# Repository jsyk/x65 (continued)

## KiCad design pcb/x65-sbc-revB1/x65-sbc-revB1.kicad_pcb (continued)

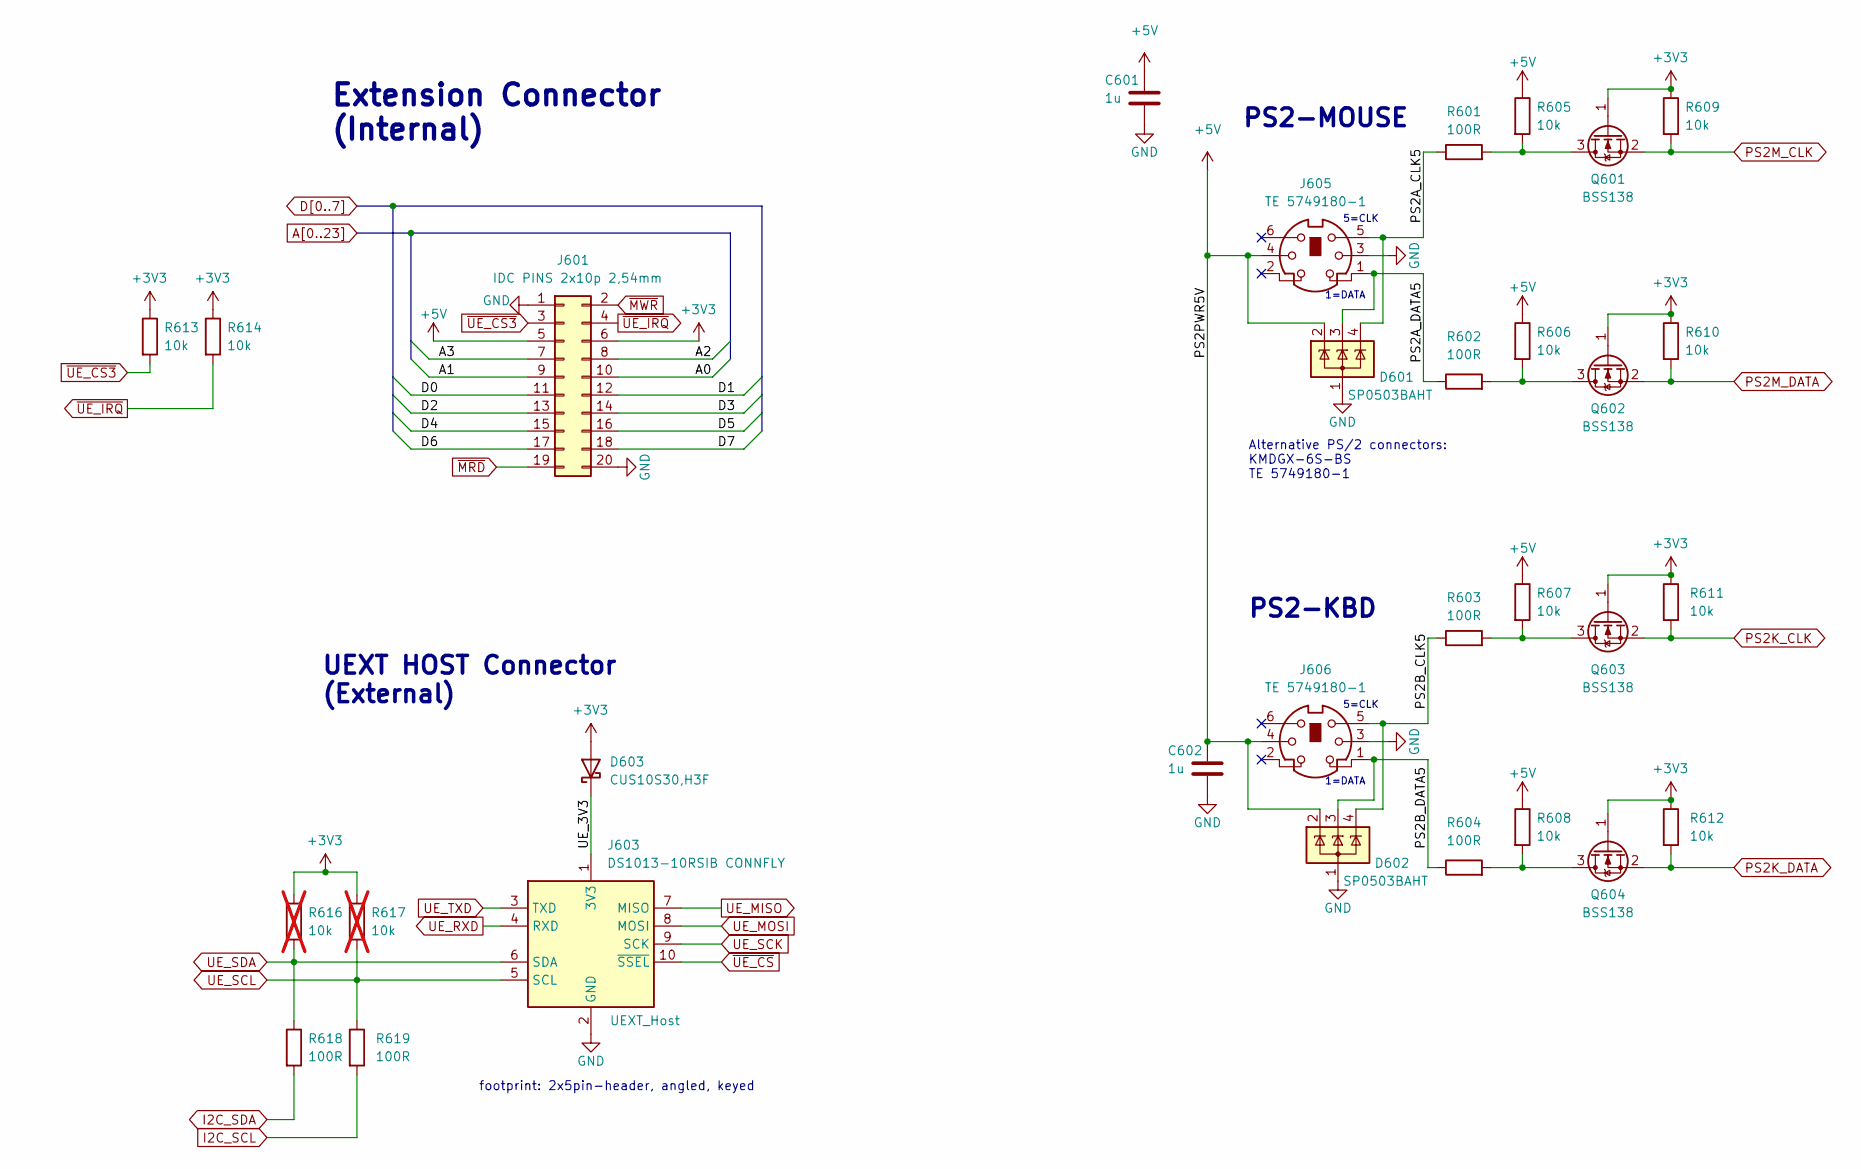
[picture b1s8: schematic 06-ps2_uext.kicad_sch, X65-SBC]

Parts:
C601, C602: 1u; C_0603_1608Metric_Pad1.08x0.95mm_HandSolder
D601, D602: SP0503BAHT; SOT-143
D603: CUS10S30,H3F; D_SOD-323_HandSoldering
J601: IDC PINS 2x10p 2,54mm; IDC-Header_2x10_P2.54mm_Vertical
J603: DS1013-10RSIB CONNFLY; IDC-Header_2x05_P2.54mm_Horizontal
J605, J606: TE 5749180-1; TE_5749180-1
Q601, Q602, Q603, Q604: BSS138; SOT-23
R601, R602, R603, R604, R618, R619: 100R; R_0603_1608Metric_Pad0.98x0.95mm_HandSolder
R605, R606, R607, R608, R609, R610, R611, R612, R613, R614: 10k; R_0603_1608Metric_Pad0.98x0.95mm_HandSolder
R616, R617: 10k; R_0603_1608Metric_Pad0.98x0.95mm_HandSolder; not fitted

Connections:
+3V3: D603.2 (A), J601.6, Q601.1 (G), Q602.1 (G), Q603.1 (G), Q604.1 (G), R609.1, R610.1, R611.1, R612.1, R613.1, R614.1, R616.1, R617.1; also elsewhere on the board
+5V: C601.1, C602.1, D601.2 (K), D602.2 (K), J601.5, J605.4, J606.4, R605.1, R606.1, R607.1, R608.1; also elsewhere on the board
/PS2 Kbd+Mouse, UEXT/PS2A_CLK5: D601.4 (K), J605.5, R601.1
/PS2 Kbd+Mouse, UEXT/PS2A_DATA5: D601.3 (K), J605.1, R602.1
/PS2 Kbd+Mouse, UEXT/PS2B_CLK5: D602.4 (K), J606.5, R603.1
/PS2 Kbd+Mouse, UEXT/PS2B_DATA5: D602.3 (K), J606.1, R604.1
/PS2 Kbd+Mouse, UEXT/UE_3V3: D603.1 (K), J603.1 (3V3)
A0: J601.10; also elsewhere on the board
A1: J601.9; also elsewhere on the board
A2: J601.8; also elsewhere on the board
A3: J601.7; also elsewhere on the board
D0: J601.11; also elsewhere on the board
D1: J601.12; also elsewhere on the board
D2: J601.13; also elsewhere on the board
D3: J601.14; also elsewhere on the board
D4: J601.15; also elsewhere on the board
D5: J601.16; also elsewhere on the board
D6: J601.17; also elsewhere on the board
D7: J601.18; also elsewhere on the board
GND: C601.2, C602.2, D601.1 (A), D602.1 (A), J601.1, J601.20, J603.2 (GND), J605.3, J606.3; also elsewhere on the board
I2C_SCL: R619.2; also elsewhere on the board
I2C_SDA: R618.2; also elsewhere on the board
unnamed: Q601.3 (D), R601.2, R605.2
unnamed: Q602.3 (D), R602.2, R606.2
unnamed: Q603.3 (D), R603.2, R607.2
unnamed: Q604.3 (D), R604.2, R608.2
PS2K_CLK: Q603.2 (S), R611.2; also elsewhere on the board
PS2K_DATA: Q604.2 (S), R612.2; also elsewhere on the board
PS2M_CLK: Q601.2 (S), R609.2; also elsewhere on the board
PS2M_DATA: Q602.2 (S), R610.2; also elsewhere on the board
UE_MISO: J603.7 (MISO); also elsewhere on the board
UE_MOSI: J603.8 (MOSI); also elsewhere on the board
UE_RXD: J603.4 (RXD); also elsewhere on the board
UE_SCK: J603.9 (SCK); also elsewhere on the board
UE_SCL: J603.5 (SCL), R617.2, R619.1; also elsewhere on the board
UE_SDA: J603.6 (SDA), R616.2, R618.1; also elsewhere on the board
UE_TXD: J603.3 (TXD); also elsewhere on the board
~MRD: J601.19; also elsewhere on the board
~MWR: J601.2; also elsewhere on the board
~UE_CS3: J601.3, R613.2; also elsewhere on the board
~UE_CS: J603.10 (~SSEL); also elsewhere on the board
~UE_IRQ: J601.4, R614.2; also elsewhere on the board

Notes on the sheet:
UEXT HOST Connector (External)
1=DATA
5=CLK
PS2-MOUSE
PS2-KBD
Extension Connector (Internal)
footprint: 2x5pin-header, angled, keyed
Alternative PS/2 connectors: KMDGX-6S-BS TE 5749180-1

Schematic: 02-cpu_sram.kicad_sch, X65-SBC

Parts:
C201, C202, C203, C204: 1u; C_0603_1608Metric_Pad1.08x0.95mm_HandSolder
R201, R202, R203, R204, R205, R207, R214, R215: 10k; R_0603_1608Metric_Pad0.98x0.95mm_HandSolder
R208, R210, R213: 0R; R_0603_1608Metric_Pad0.98x0.95mm_HandSolder
R211: 50R; R_0603_1608Metric_Pad0.98x0.95mm_HandSolder
R212: 100R; R_0603_1608Metric_Pad0.98x0.95mm_HandSolder
R216: 10k; R_0603_1608Metric_Pad0.98x0.95mm_HandSolder; not fitted
R217: 2k; R_0603_1608Metric_Pad0.98x0.95mm_HandSolder
U201: W65C816S6TQG-14; MQFP-44_10x10mm_P0.8mm
U202: IS61WV20488FBLL-10TLI; TSOP-II-44_10.16x18.41mm_P0.8mm

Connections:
+3V3: C201.1, C202.1, C203.1, C204.1, R201.1, R202.1, R203.1, R204.1, R214.1, R216.1, U201.3 (VDD), U201.31 (VDD), U202.11 (VDD), U202.33 (VDD); also elsewhere on the board
A0: U201.4 (A0), U202.3 (A0); also elsewhere on the board
A1: U201.5 (A1), U202.4 (A1); also elsewhere on the board
A2: U201.7 (A2), U202.5 (A2); also elsewhere on the board
A3: U201.8 (A3), U202.6 (A3); also elsewhere on the board
A4: U201.9 (A4), U202.7 (A4); also elsewhere on the board
A5: U201.10 (A5), U202.16 (A5); also elsewhere on the board
A6: U201.11 (A6), U202.17 (A6); also elsewhere on the board
A7: U201.12 (A7), U202.18 (A7); also elsewhere on the board
A8: U201.13 (A8), U202.19 (A8); also elsewhere on the board
A9: U201.14 (A9), U202.20 (A9); also elsewhere on the board
A10: U201.15 (A10), U202.26 (A10); also elsewhere on the board
A11: U201.16 (A11), U202.27 (A11); also elsewhere on the board
A12: U202.28 (A12); also elsewhere on the board
A13: U202.29 (A13); also elsewhere on the board
A14: U202.30 (A14); also elsewhere on the board
A15: U202.38 (A15); also elsewhere on the board
A16: U202.39 (A16); also elsewhere on the board
A17: U202.40 (A17); also elsewhere on the board
A18: U202.41 (A18); also elsewhere on the board
A19: U202.25 (A19); also elsewhere on the board
A20: U202.42 (A20); also elsewhere on the board
CA12: U201.19 (A12); also elsewhere on the board
CA13: U201.20 (A13); also elsewhere on the board
CA14: U201.21 (A14); also elsewhere on the board
CA15: U201.22 (A15); also elsewhere on the board
CBE: R205.1, U201.34 (BE); also elsewhere on the board
CD0: U201.30 (D0); also elsewhere on the board
CD1: U201.29 (D1); also elsewhere on the board
CD2: U201.28 (D2); also elsewhere on the board
CD3: U201.27 (D3); also elsewhere on the board
CD4: U201.26 (D4); also elsewhere on the board
CD5: U201.25 (D5); also elsewhere on the board
CD6: U201.24 (D6); also elsewhere on the board
CD7: U201.23 (D7); also elsewhere on the board
CEF: R202.2, R210.1; also elsewhere on the board
CPHI2: R211.1; also elsewhere on the board
CPUTYPE02: R216.2, R217.1; also elsewhere on the board
CRDY: R212.2, R214.2; also elsewhere on the board
CSOB_MX: R204.2, U201.36 (SOB/MX); also elsewhere on the board
CSYNC_VPA: U201.2 (SYNC/VPA); also elsewhere on the board
CVDA: R213.2, R215.1; also elsewhere on the board
D0: U202.9 (D0); also elsewhere on the board
D1: U202.10 (D1); also elsewhere on the board
D2: U202.13 (D2); also elsewhere on the board
D3: U202.14 (D3); also elsewhere on the board
D4: U202.31 (D4); also elsewhere on the board
D5: U202.32 (D5); also elsewhere on the board
D6: U202.35 (D6); also elsewhere on the board
D7: U202.36 (D7); also elsewhere on the board
GND: C201.2, C202.2, C203.2, C204.2, R205.2, R207.2, R215.2, R217.2, U201.17 (VSS), U201.18 (VSS), U201.39 (VSS), U202.12 (VSS), U202.34 (VSS); also elsewhere on the board
unnamed: R210.2, U201.33 (NC/E)
unnamed: R208.2, U201.42 (PHI1O/ABORTB)
unnamed: R211.2, U201.35 (PHI2)
unnamed: R213.1, U201.37 (PHI2O/VDA)
unnamed: R212.1, U201.41 (RDY)
~CABORT: R203.2, R208.1; also elsewhere on the board
~CIRQ: U201.43 (IRQB); also elsewhere on the board
~CML: U201.44 (MLB); also elsewhere on the board
~CNMI: U201.1 (NMIB); also elsewhere on the board
~CRES: R207.1, U201.38 (RESB); also elsewhere on the board
~CRW: U201.32 (RWB); also elsewhere on the board
~CVP: U201.40 (VPB); also elsewhere on the board
~M1CS: R201.2, U202.8 (CS#); also elsewhere on the board
~MRD: U202.37 (OE#); also elsewhere on the board
~MWR: U202.15 (WE#); also elsewhere on the board

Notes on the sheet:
R216 assemble just in case CPU=65C02
CD[0..7] => only to "NORA" FPGA
CPU
CPU U201 assembly options: a) W65C02S6TQG-14 => 8-bit CPU => do not populate R208, R210, R213, R217. => do populate R216 (so that CPUTYPE02=Hi) b) W65C816S6TQG-14 => 16-bit CPU => as shown in the schematic.
44-pin TSOP Type-II package
MQFP-44 package
R217 assemble just in case CPU=65C816
RAM
DEFAULT

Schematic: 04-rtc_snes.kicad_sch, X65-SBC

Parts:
BT401: BAT-HLD-012-SMT; BatteryHolder_LINX_BAT-HLD-012-SMT
C401, C404: 1u; C_0603_1608Metric_Pad1.08x0.95mm_HandSolder
C402, C403: 18p; C_0603_1608Metric_Pad1.08x0.95mm_HandSolder
D401: CUS10S30,H3F; D_SOD-323_HandSoldering
D402: AA4040LCGCK-AMT; PLCC2_4x4mm
D403: AA4040SESK; PLCC2_4x4mm
D404, D405: SP0503BAHT; SOT-143
D406, D407: LED_YELLOW_0603; LED_0603_1608Metric_Pad1.05x0.95mm_HandSolder
J403, J404: SNES_Controller_Conn; SNES_Controller_Conn_7p_90deg_P1Left
R401, R413, R421, R422: 33k; R_0603_1608Metric_Pad0.98x0.95mm_HandSolder
R402, R414, R417, R418, R419, R420: 2k7; R_0603_1608Metric_Pad0.98x0.95mm_HandSolder
R403, R404, R411, R412: 10k; R_0603_1608Metric_Pad0.98x0.95mm_HandSolder
R405, R406, R407, R408, R409, R410: 100R; R_0603_1608Metric_Pad0.98x0.95mm_HandSolder
R415, R416: 470R; R_0603_1608Metric_Pad0.98x0.95mm_HandSolder
SW401: SW_DIP_x02 TE 1825058-1; SW_DIP_SPSTx02_Slide_6.7x6.64mm_W8.61mm_P2.54mm_LowProfile
U401, U403: 74LVC2G17DBVR; SOT-23-6_Handsoldering
U402: MCP7940N-xSN; SO-8_3.9x4.9mm_P1.27mm
Y402: CM8V-T1A-32.768kHz-9pF-20PPM-TA-QC; Crystal_SMD_MicroCrystal_CC8V-T1A-2Pin_2.0x1.2mm_HandSolder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

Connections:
+3V3: D402.2 (A), D403.2 (A), D406.2 (A), D407.2 (A), R401.2, R403.2, R404.2, R413.2, R421.2, R422.2, U401.5 (VCC), U402.8 (VCC); also elsewhere on the board
+5V: C404.1, J403.1 (V+5V), J404.1 (V+5V), R411.2, R412.2, U403.5 (VCC); also elsewhere on the board
/LEDs, RTC, SNES/NES0DATA5: R409.1, R411.1, U401.1
/LEDs, RTC, SNES/NES1DATA5: R410.1, R412.1, U401.3
/LEDs, RTC, SNES/NESCLOCK5: R405.1, R407.1, U403.4
/LEDs, RTC, SNES/NESLATCH5: R406.1, R408.1, U403.6
/LEDs, RTC, SNES/VBAT3V: C401.1, D401.1 (K), U402.3 (VBAT)
CPULED0: R401.1, R402.2, R415.1; also elsewhere on the board
CPULED1: R413.1, R414.2, R416.1; also elsewhere on the board
DIPLED0: R417.2, R419.1, R421.1; also elsewhere on the board
DIPLED1: R418.2, R420.1, R422.1; also elsewhere on the board
GND: BT401.2 (-), C401.2, C402.2, C403.2, C404.2, D404.1 (A), D405.1 (A), J403.7 (GND), J404.7 (GND), SW401.1, SW401.2, U401.2 (GND), U402.4 (VSS), U403.2 (GND); also elsewhere on the board
I2C_SCL: R403.1, U402.6 (SCL); also elsewhere on the board
I2C_SDA: R404.1, U402.5 (SDA); also elsewhere on the board
NESCLOCK: U403.3; also elsewhere on the board
NESDATA0: U401.6; also elsewhere on the board
NESDATA1: U401.4; also elsewhere on the board
NESLATCH: U403.1; also elsewhere on the board
unnamed: BT401.1 (+), D401.2 (A)
unnamed: D402.1 (K), R415.2
unnamed: D403.1 (K), R416.2
unnamed: D406.1 (K), R419.2
unnamed: D407.1 (K), R420.2
unnamed: D404.2 (K), J403.2 (CLOCK), R405.2
unnamed: D404.4 (K), J403.4 (DATA1), R409.2
unnamed: D404.3 (K), J403.3 (LATCH), R406.2
unnamed: D405.2 (K), J404.2 (CLOCK), R407.2
unnamed: D405.3 (K), J404.4 (DATA1), R410.2
unnamed: D405.4 (K), J404.3 (LATCH), R408.2
unnamed: R417.1, SW401.4
unnamed: R418.1, SW401.3
unnamed: C403.1, U402.1 (X1), Y402.2
unnamed: C402.1, U402.2 (X2), Y402.1
SD_WP: R414.1; also elsewhere on the board
~SD_CD: R402.1; also elsewhere on the board

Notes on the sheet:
RTC
SMD
RTC/MCP7940N I2C DEVICE ADDRESS (8b=shifted) = 0b1101_111W = 0xDE, that is 7-bit addr 0x6F PS2 CONTROLLER (IN NORA) I2C DEVICE ADDRESS (8b=shifted) = 0b1000010W = 0x84, that is 7-bit addr 0x42
2x SNES JOYPAD CONTROLLER PORTS
2x package: SOT-23-6
User LEDs
ORANGE REFLECTOR LED
Battery holder for CR1216/1225 3V cell
SNES CONTROLLER EXAMPLE:
MCP7940N datasheet says: * crystal loading shall be 6-9pf; 12pf not recommended! * CX should be 2* X_loading, so that in parallel the crystal see the expected capacitance * layout must be according to the DS.
GREEN REFLECTOR LED
package: SOIC-8 150mil
package: SOT-23-6
J403, J404 TYPE:
Dual purpose CPULED0/1 signals: a) CPULED0/1 configured as OUTPUT DRIVING: set 0 => LED ON set 1 => LED OFF b) CPULED0/1 configured as INPUT: read 0 => switch SD_CD or SD_WP closed. read 1 => switch SD_CD or SD_WP open.

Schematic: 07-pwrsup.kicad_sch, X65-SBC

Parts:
C701, C702, C703, C704: 22u/16V; C_0805_2012Metric_Pad1.18x1.45mm_HandSolder
C705: 1u; C_0603_1608Metric_Pad1.08x0.95mm_HandSolder
D701: LED_GREEN_0603; LED_0603_1608Metric_Pad1.05x0.95mm_HandSolder
J701: Conn_01x02; PinHeader_1x02_P2.54mm_Vertical; not fitted
J702, J703, J704: Conn_01x01; PinHeader_1x01_P2.54mm_Vertical; not fitted
JP701, JP702: SolderJumper_2_Bridged; SolderJumper-2_P1.3mm_Open_RoundedPad1.0x1.5mm
L701: DFE252010P-2R2M=P2; L_1008_2520Metric_Pad1.43x2.20mm_HandSolder
L702: DFE252010P-1R0M=P2; L_1008_2520Metric_Pad1.43x2.20mm_HandSolder
R701: 12k; R_0603_1608Metric_Pad0.98x0.95mm_HandSolder
R702, R707: 2k7; R_0603_1608Metric_Pad0.98x0.95mm_HandSolder
R703, R706: 10R; R_0603_1608Metric_Pad0.98x0.95mm_HandSolder
R704, R705, R708: 10k; R_0603_1608Metric_Pad0.98x0.95mm_HandSolder
U701: MP2149GJ; TSOT-23-8_HandSoldering

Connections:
+1V2: JP702.2 (B); also elsewhere on the board
+3V3: D701.2 (A), JP701.2 (B); also elsewhere on the board
+5V: C701.1, C704.2, J701.2, R708.1, U701.2 (EN2), U701.7 (IN); also elsewhere on the board
/Power Supply/EN3V3: C705.1, R708.2, U701.4 (EN1)
/Power Supply/FB1: R701.2, R702.1, U701.8 (FB1)
/Power Supply/FB2: R704.2, R705.1, U701.1 (FB2)
/Power Supply/RAW1V2: C703.2, JP702.1 (A), L702.2, R706.1
/Power Supply/RAW3V3: C702.2, JP701.1 (A), L701.1, R703.1
/Power Supply/SW1: L701.2, U701.6 (SW1)
/Power Supply/SW2: L702.1, U701.3 (SW2)
GND: C701.2, C702.1, C703.1, C704.1, C705.2, J701.1, J702.1, J703.1, J704.1, R702.2, R705.2, R707.2, U701.5 (GND); also elsewhere on the board
unnamed: D701.1 (K), R707.1
unnamed: R701.1, R703.2
unnamed: R704.1, R706.2

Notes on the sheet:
1uH
2,2uH
"POWER ON" GREEN REFLECTOR LED
POWER SUPPLY 5V -> 3.3V, 1.2V
1V2 consumption: 20mA
GND testpoints
package: TSOT-23-8
Close JP701, JP702 by solder after testing the PSU.
Alternative power input connector
R708/C705 delays 3V3 start by 10ms (FPGA seq. requirement: first 1V2, then 3V3)
3V3 consumption: 80mA to 300mA

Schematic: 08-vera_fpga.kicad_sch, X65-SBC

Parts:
C801, C802, C803, C804, C805, C806: 1u; C_0603_1608Metric_Pad1.08x0.95mm_HandSolder
D801: LED_GREEN_0603; LED_0603_1608Metric_Pad1.05x0.95mm_HandSolder
D802: CUS10S30,H3F; D_SOD-323_HandSoldering
J801: ICD15S13E4GV00LF
Q801: BSS138; SOT-23
R802, R803, R831: 10k; R_0603_1608Metric_Pad0.98x0.95mm_HandSolder
R804: 2k7; R_0603_1608Metric_Pad0.98x0.95mm_HandSolder
R805, R806: 50R; R_0603_1608Metric_Pad0.98x0.95mm_HandSolder
R808, R812, R816: 510R; R_0603_1608Metric_Pad0.98x0.95mm_HandSolder
R809, R813, R817: 910R; R_0603_1608Metric_Pad0.98x0.95mm_HandSolder
R810, R814, R818: 2k; R_0603_1608Metric_Pad0.98x0.95mm_HandSolder
R811, R815, R819: 4k3; R_0603_1608Metric_Pad0.98x0.95mm_HandSolder
R820, R823, R826: 27R; R_0603_1608Metric_Pad0.98x0.95mm_HandSolder
R821, R824, R827: 160R; R_0603_1608Metric_Pad0.98x0.95mm_HandSolder
R822, R825, R828: 150R; R_0603_1608Metric_Pad0.98x0.95mm_HandSolder
R829, R830: 820R; R_0603_1608Metric_Pad0.98x0.95mm_HandSolder
U801: ICE40UP5K-SG48ITR50; QFN-48-1EP_7x7mm_P0.5mm_EP5.3x5.3mm
X801: SG5032CAN_25.000000M-TJGA3; Oscillator_SMD_SeikoEpson_SG8002LB-4Pin_5.0x3.2mm_HandSolde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

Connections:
25MHz: R805.1, R806.1, X801.3 (OUT); also elsewhere on the board
+1V2: C801.1, C803.1, U801.5 (VCC), U801.29 (VCCPLL), U801.30 (VCC); also elsewhere on the board
+3V3: C802.1, C804.1, C805.1, C806.1, D801.2 (A), D802.2 (A), R802.1, R803.1, R831.1, U801.1 (VCCIO_2), U801.22 (SPI_VCCIO1), U801.33 (VCCIO_0), X801.4 (VCC); also elsewhere on the board
+5V: J801.9; also elsewhere on the board
/VERA FPGA/BLUE: J801.3, R819.1, R826.1, R827.1, R828.1
/VERA FPGA/GREEN: J801.2, R815.1, R823.1, R824.1, R825.1
/VERA FPGA/HSYNC: J801.13, R830.1
/VERA FPGA/RED: J801.1, R811.1, R820.1, R821.1, R822.1
/VERA FPGA/VSYNC: J801.14, R829.1
A0: U801.40 (RGB1); also elsewhere on the board
A1: U801.39 (RGB0); also elsewhere on the board
A2: U801.37 (IOT_45A_G1); also elsewhere on the board
A3: U801.41 (RGB2); also elsewhere on the board
A4: U801.34 (IOT_44B); also elsewhere on the board
ASYSCLK: R806.2; also elsewhere on the board
D0: U801.27 (IOT_38B); also elsewhere on the board
D1: U801.26 (IOT_39A); also elsewhere on the board
D2: U801.25 (IOT_36B); also elsewhere on the board
D3: U801.23 (IOT_37A); also elsewhere on the board
D4: U801.21 (IOB_23B); also elsewhere on the board
D5: U801.20 (IOB_25B_G3); also elsewhere on the board
D6: U801.19 (IOB_29B); also elsewhere on the board
D7: U801.18 (IOB_31B); also elsewhere on the board
GND: C801.2, C802.2, C803.2, C804.2, C805.2, C806.2, J801.0, J801.5, J801.6, J801.7, J801.8, J801.10, Q801.2 (S), U801.49 (GND), X801.2 (GND); also elsewhere on the board
unnamed: D801.1 (K), R804.2
unnamed: D802.1 (K), U801.24 (VPP_2V5)
unnamed: Q801.3 (D), R804.1
unnamed: R808.1, R820.2
unnamed: R809.1, R821.2
unnamed: R810.1, R822.2
unnamed: R812.1, R823.2
unnamed: R813.1, R824.2
unnamed: R814.1, R825.2
unnamed: R816.1, R826.2
unnamed: R817.1, R827.2
unnamed: R818.1, R828.2
VAUDIO_BCK: U801.38 (IOT_50B); also elsewhere on the board
VAUDIO_DATA: U801.42 (IOT_51A); also elsewhere on the board
VAUDIO_LRCK: U801.43 (IOT_49A); also elsewhere on the board
VFPGA_CDONE: Q801.1 (G), R803.2, U801.7 (CDONE); also elsewhere on the board
VGA_B0: R819.2, U801.46 (IOB_0A)
VGA_B1: R818.2, U801.47 (IOB_2A)
VGA_B2: R817.2, U801.48 (IOB_4A)
VGA_B3: R816.2, U801.2 (IOB_6A)
VGA_G0: R815.2, U801.3 (IOB_9B)
VGA_G1: R814.2, U801.4 (IOB_8A)
VGA_G2: R813.2, U801.6 (IOB_13B)
VGA_G3: R812.2, U801.9 (IOB_16A)
VGA_HSYNC: R830.2, U801.44 (IOB_3B_G6)
VGA_R0: R811.2, U801.10 (IOB_18A)
VGA_R1: R810.2, U801.11 (IOB_20A)
VGA_R2: R809.2, U801.12 (IOB_22A)
VGA_R3: R808.2, U801.13 (IOB_24A)
VGA_VSYNC: R829.2, U801.45 (IOB_5B)
VSPI_MISO: U801.17 (IOB_33B_SPI_SI); also elsewhere on the board
VSPI_MOSI: U801.14 (IOB_32A_SPI_SO); also elsewhere on the board
VSPI_SCK: U801.15 (IOB_34A_SPI_SCK); also elsewhere on the board
VSYSCLK: R805.2, U801.35 (IOT_46B_G0)
~MRD: U801.36 (IOT_48B); also elsewhere on the board
~MWR: U801.31 (IOT_42B); also elsewhere on the board
~VCS0: U801.28 (IOT_41A); also elsewhere on the board
~VIRQ: R831.2, U801.32 (IOT_43A); also elsewhere on the board
~VRST: R802.2, U801.8 (CRESET_B); also elsewhere on the board
~VSPI_SSEL: U801.16 (IOB_35B_SPI_SS); also elsewhere on the board

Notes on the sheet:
"VERA" FPGA - Video Embedded Retro Adapter
VGA interface
(orig: 536R)
package: SOT-23
package QFN-48
"VERA READY" internal LED
This schematic contains portions of work done by Frank van den Hoe for the project VERA: https://github.com/fvdhoef/vera-module
Common 25MHz oscillator
(orig:536R)

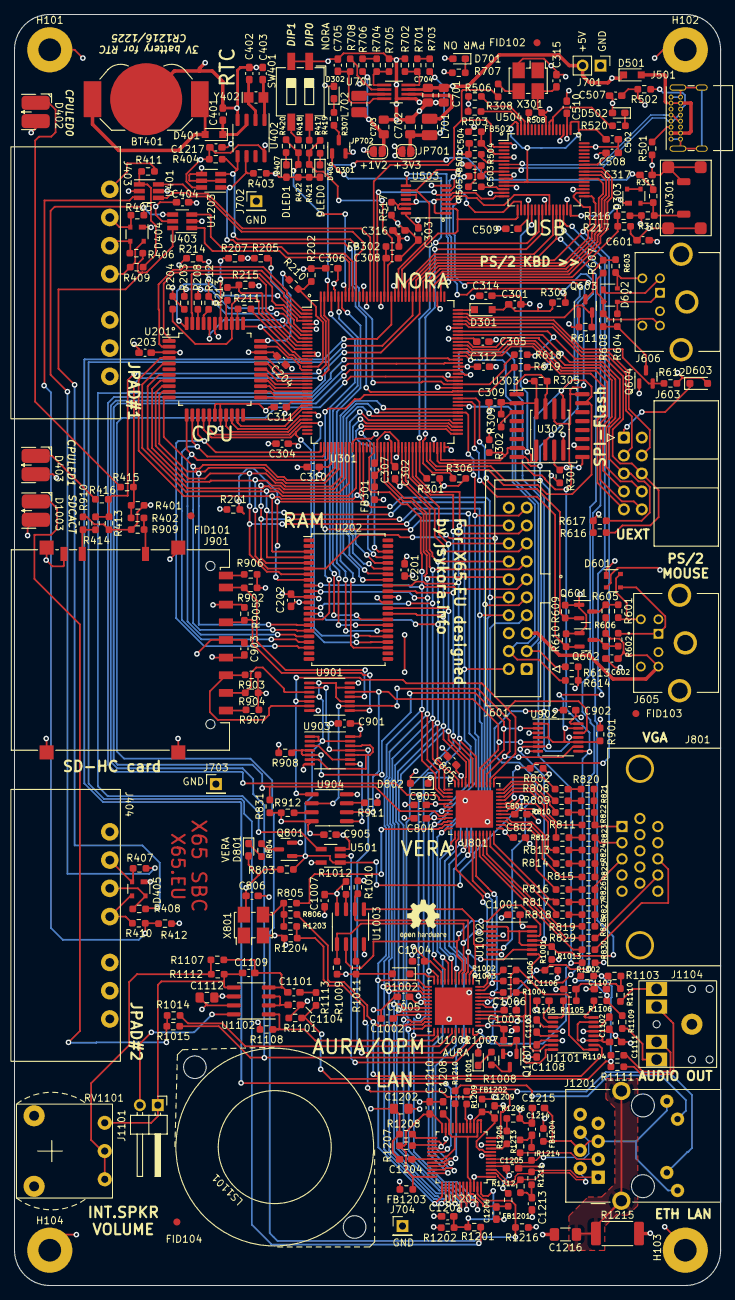
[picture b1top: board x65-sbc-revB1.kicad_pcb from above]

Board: 4 copper layers, 100.0 x 180.0 mm, 343 parts (0 on the bottom side), 299 nets.

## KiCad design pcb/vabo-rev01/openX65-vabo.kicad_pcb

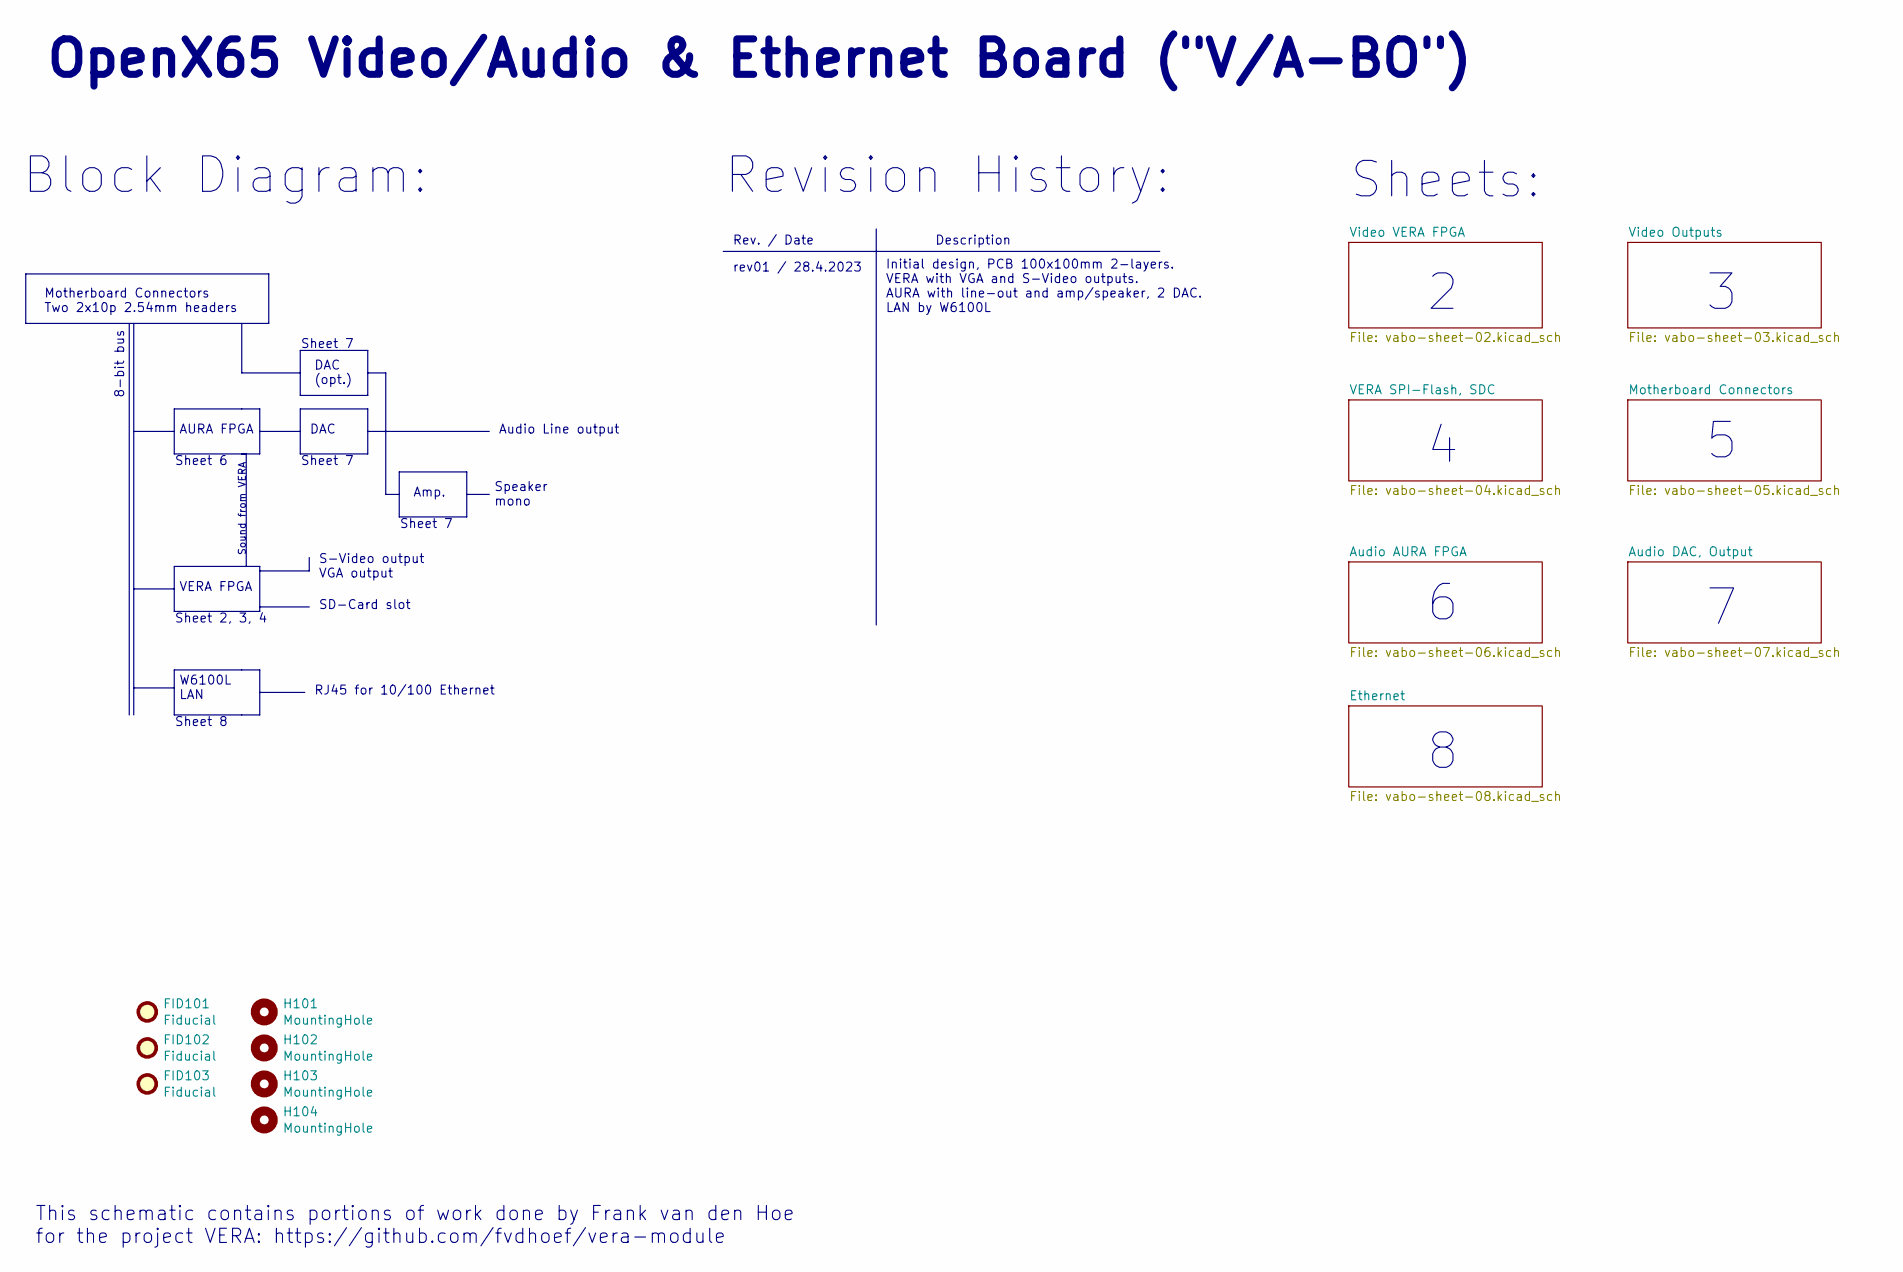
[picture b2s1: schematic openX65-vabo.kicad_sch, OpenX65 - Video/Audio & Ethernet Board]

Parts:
FID101, FID102, FID103: Fiducial; Fiducial_1mm_Mask2mm
H101, H102, H103, H104: MountingHole; MountingHole_3.2mm_M3

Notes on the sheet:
Amp.
Sheet 7
Sheet 6
Motherboard Connectors Two 2x10p 2.54mm headers
8-bit bus
RJ45 for 10/100 Ethernet
DAC
Sheets:
OpenX65 Video/Audio & Ethernet Board ("V/A-BO")
SD-Card slot
Initial design, PCB 100x100mm 2-layers. VERA with VGA and S-Video outputs. AURA with line-out and amp/speaker, 2 DAC. LAN by W6100L
Sheet 2, 3, 4
W6100L LAN
Speaker mono
S-Video output VGA output
Sheet 8
VERA FPGA
Revision History:
Description
Audio Line output
Sound from VERA
AURA FPGA
rev01 / 28.4.2023
Rev. / Date
Block Diagram:
DAC (opt.)
This schematic contains portions of work done by Frank van den Hoe for the project VERA: https://github.com/fvdhoef/vera-module

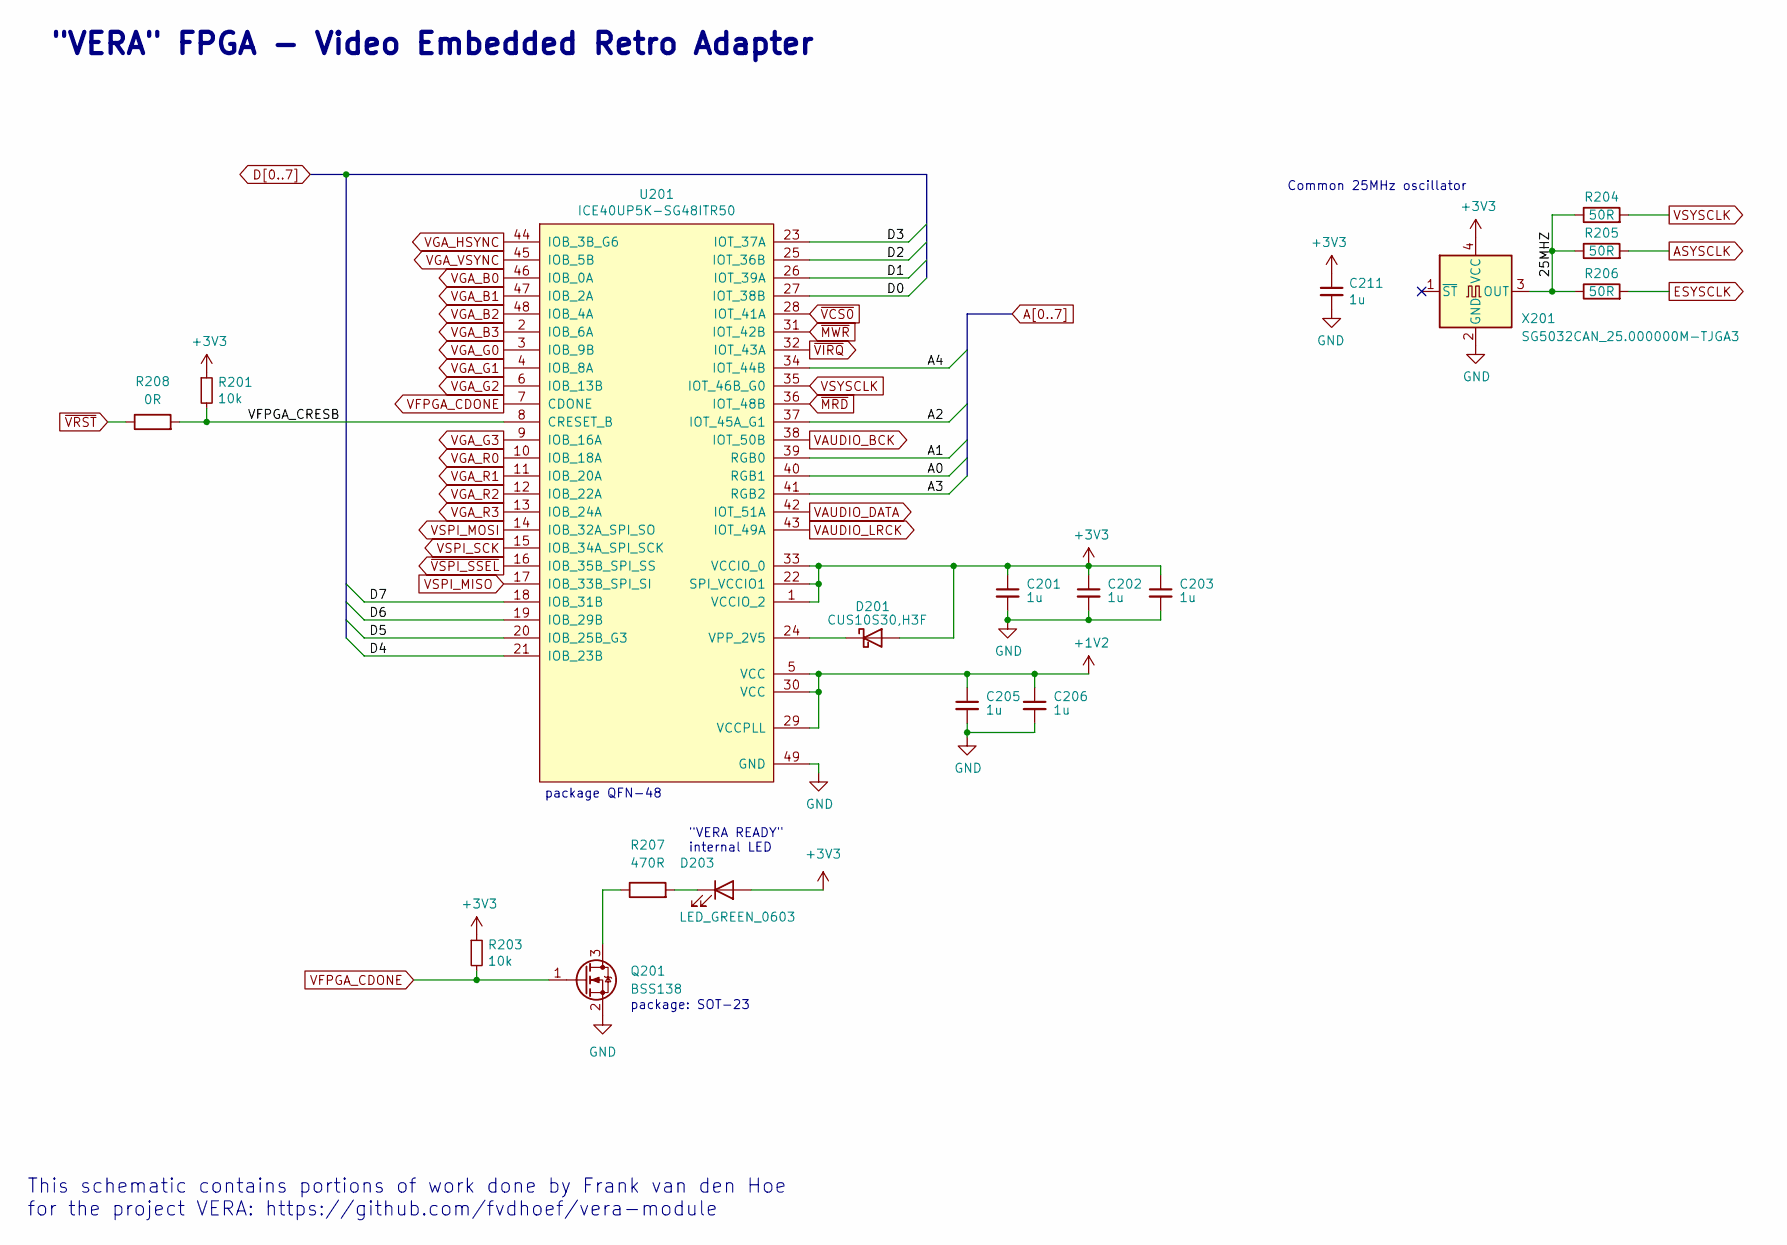
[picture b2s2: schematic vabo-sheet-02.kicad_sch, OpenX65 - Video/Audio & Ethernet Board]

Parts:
C201, C202, C203, C205, C206, C211: 1u; C_0603_1608Metric_Pad1.08x0.95mm_HandSolder
D201: CUS10S30,H3F; D_SOD-323_HandSoldering
D203: LED_GREEN_0603; LED_0603_1608Metric_Pad1.05x0.95mm_HandSolder
Q201: BSS138; SOT-23
R201, R203: 10k; R_0603_1608Metric_Pad0.98x0.95mm_HandSolder
R204, R205, R206: 50R; R_0603_1608Metric_Pad0.98x0.95mm_HandSolder
R207: 470R; R_0603_1608Metric_Pad0.98x0.95mm_HandSolder
R208: 0R; R_0603_1608Metric_Pad0.98x0.95mm_HandSolder
U201: ICE40UP5K-SG48ITR50; QFN-48-1EP_7x7mm_P0.5mm_EP5.3x5.3mm
X201: SG5032CAN_25.000000M-TJGA3; Oscillator_SMD_SeikoEpson_SG8002LB-4Pin_5.0x3.2mm_HandSolde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

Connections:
+1V2: C205.1, C206.1, U201.5 (VCC), U201.29 (VCCPLL), U201.30 (VCC); also elsewhere on the board
+3V3: C201.1, C202.1, C203.1, C211.1, D201.2 (A), D203.2 (A), R201.1, R203.1, U201.1 (VCCIO_2), U201.22 (SPI_VCCIO1), U201.33 (VCCIO_0), X201.4 (VCC); also elsewhere on the board
/Video VERA FPGA/25MHZ: R204.1, R205.1, R206.1, X201.3 (OUT)
/Video VERA FPGA/VFPGA_CRESB: R201.2, R208.2, U201.8 (CRESET_B)
A0: U201.40 (RGB1); also elsewhere on the board
A1: U201.39 (RGB0); also elsewhere on the board
A2: U201.37 (IOT_45A_G1); also elsewhere on the board
A3: U201.41 (RGB2); also elsewhere on the board
A4: U201.34 (IOT_44B); also elsewhere on the board
ASYSCLK: R205.2; also elsewhere on the board
D0: U201.27 (IOT_38B); also elsewhere on the board
D1: U201.26 (IOT_39A); also elsewhere on the board
D2: U201.25 (IOT_36B); also elsewhere on the board
D3: U201.23 (IOT_37A); also elsewhere on the board
D4: U201.21 (IOB_23B); also elsewhere on the board
D5: U201.20 (IOB_25B_G3); also elsewhere on the board
D6: U201.19 (IOB_29B); also elsewhere on the board
D7: U201.18 (IOB_31B); also elsewhere on the board
ESYSCLK: R206.2; also elsewhere on the board
GND: C201.2, C202.2, C203.2, C205.2, C206.2, C211.2, Q201.2 (S), U201.49 (GND), X201.2 (GND); also elsewhere on the board
unnamed: D201.1 (K), U201.24 (VPP_2V5)
unnamed: D203.1 (K), R207.2
unnamed: Q201.3 (D), R207.1
VAUDIO_BCK: U201.38 (IOT_50B); also elsewhere on the board
VAUDIO_DATA: U201.42 (IOT_51A); also elsewhere on the board
VAUDIO_LRCK: U201.43 (IOT_49A); also elsewhere on the board
VFPGA_CDONE: Q201.1 (G), R203.2, U201.7 (CDONE); also elsewhere on the board
VGA_B0: U201.46 (IOB_0A); also elsewhere on the board
VGA_B1: U201.47 (IOB_2A); also elsewhere on the board
VGA_B2: U201.48 (IOB_4A); also elsewhere on the board
VGA_B3: U201.2 (IOB_6A); also elsewhere on the board
VGA_G0: U201.3 (IOB_9B); also elsewhere on the board
VGA_G1: U201.4 (IOB_8A); also elsewhere on the board
VGA_G2: U201.6 (IOB_13B); also elsewhere on the board
VGA_G3: U201.9 (IOB_16A); also elsewhere on the board
VGA_HSYNC: U201.44 (IOB_3B_G6); also elsewhere on the board
VGA_R0: U201.10 (IOB_18A); also elsewhere on the board
VGA_R1: U201.11 (IOB_20A); also elsewhere on the board
VGA_R2: U201.12 (IOB_22A); also elsewhere on the board
VGA_R3: U201.13 (IOB_24A); also elsewhere on the board
VGA_VSYNC: U201.45 (IOB_5B); also elsewhere on the board
VSPI_MISO: U201.17 (IOB_33B_SPI_SI); also elsewhere on the board
VSPI_MOSI: U201.14 (IOB_32A_SPI_SO); also elsewhere on the board
VSPI_SCK: U201.15 (IOB_34A_SPI_SCK); also elsewhere on the board
VSYSCLK: R204.2, U201.35 (IOT_46B_G0)
~MRD: U201.36 (IOT_48B); also elsewhere on the board
~MWR: U201.31 (IOT_42B); also elsewhere on the board
~VCS0: U201.28 (IOT_41A); also elsewhere on the board
~VIRQ: U201.32 (IOT_43A); also elsewhere on the board
~VRST: R208.1; also elsewhere on the board
~VSPI_SSEL: U201.16 (IOB_35B_SPI_SS); also elsewhere on the board

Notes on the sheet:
"VERA" FPGA - Video Embedded Retro Adapter
package: SOT-23
package QFN-48
"VERA READY" internal LED
This schematic contains portions of work done by Frank van den Hoe for the project VERA: https://github.com/fvdhoef/vera-module
Common 25MHz oscillator
